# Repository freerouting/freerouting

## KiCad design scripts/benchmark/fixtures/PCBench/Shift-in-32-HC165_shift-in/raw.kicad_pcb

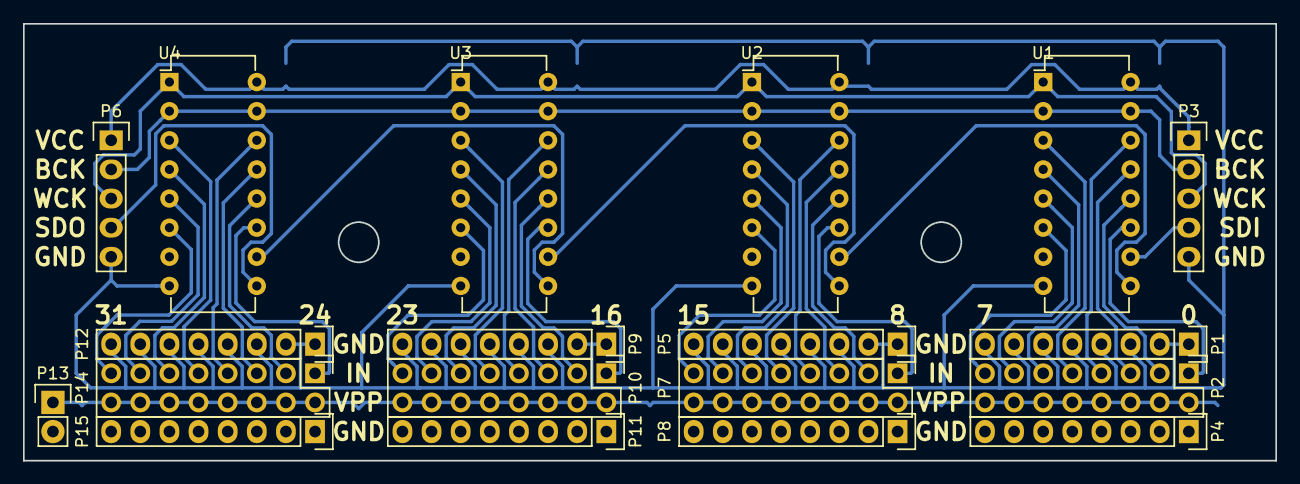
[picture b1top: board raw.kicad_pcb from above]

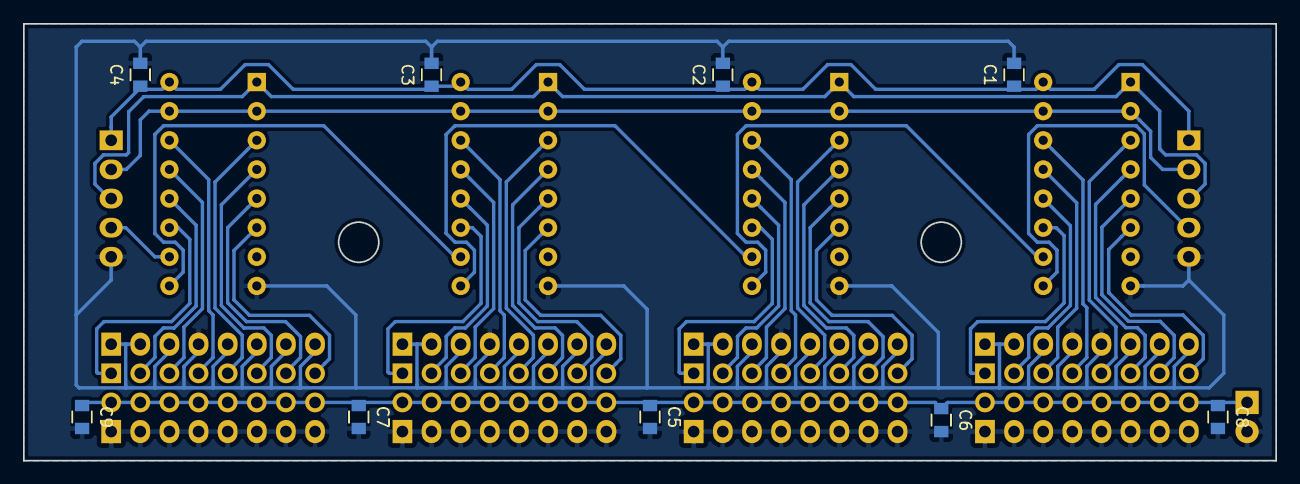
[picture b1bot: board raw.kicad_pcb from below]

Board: 2 copper layers, 109.2 x 38.1 mm, 28 parts (9 on the bottom side), 42 nets.

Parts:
C1, C2, C3, C4, C5, C6, C7, C8, C9: 10uF; C_0805
P1, P4, P5, P8, P9, P11, P12, P15: CONN_01X08; Pin_Header_Straight_1x08
P2, P7, P10, P14: CONN_02X08; Pin_Header_Straight_2x08
P3: EXPANSION; Pin_Header_Straight_1x05
P6: OUTPUT; Pin_Header_Straight_1x05
P13: CONN_01X02; Pin_Header_Straight_1x02
U1, U2, U3, U4: 74HC165; DIP-16_W7.62mm

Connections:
/BCK: P3.2, P6.2, U1.2, U1.15, U2.2, U2.15, U3.2, U3.15, U4.2, U4.15
/IN0: P2.1, U1.11
/IN1: P2.3, U1.12
/IN2: P2.5, U1.13
/IN3: P2.7, U1.14
/IN4: P2.9, U1.3
/IN5: P2.11, U1.4
/IN6: P2.13, U1.5
/IN7: P2.15, U1.6
/IN8: P7.1, U2.11
/IN9: P7.3, U2.12
/IN10: P7.5, U2.13
/IN11: P7.7, U2.14
/IN12: P7.9, U2.3
/IN13: P7.11, U2.4
/IN14: P7.13, U2.5
/IN15: P7.15, U2.6
/IN16: P10.1, U3.11
/IN17: P10.3, U3.12
/IN18: P10.5, U3.13
/IN19: P10.7, U3.14
/IN20: P10.9, U3.3
/IN21: P10.11, U3.4
/IN22: P10.13, U3.5
/IN23: P10.15, U3.6
/IN24: P14.1, U4.11
/IN25: P14.3, U4.12
/IN26: P14.5, U4.13
/IN27: P14.7, U4.14
/IN28: P14.9, U4.3
/IN29: P14.11, U4.4
/IN30: P14.13, U4.5
/IN31: P14.15, U4.6
/SDI: P3.4, U1.10
/SDO: P6.4, U4.9
/WCK: P3.3, P6.3, U1.1, U2.1, U3.1, U4.1
GND: C1.2, C2.2, C3.2, C4.2, C5.2, C6.2, C7.2, C8.2, C9.2, P1.1, P1.2, P1.3, P1.4, P1.5, P1.6, P1.7, P1.8, P3.5, P4.1, P4.2, P4.3, P4.4, P4.5, P4.6, P4.7, P4.8, P5.1, P5.2, P5.3, P5.4, P5.5, P5.6, P5.7, P5.8, P6.5, P8.1, P8.2, P8.3, P8.4, P8.5, P8.6, P8.7, P8.8, P9.1, P9.2, P9.3, P9.4, P9.5, P9.6, P9.7, P9.8, P11.1, P11.2, P11.3, P11.4, P11.5, P11.6, P11.7, P11.8, P12.1, P12.2, P12.3, P12.4, P12.5, P12.6, P12.7, P12.8, P13.2, P15.1, P15.2, P15.3, P15.4, P15.5, P15.6, P15.7, P15.8, U1.8, U2.8, U3.8, U4.8
unnamed: U1.9, U2.10
unnamed: U2.9, U3.10
unnamed: U3.9, U4.10
VCC: C1.1, C2.1, C3.1, C4.1, P3.1, P6.1, U1.16, U2.16, U3.16, U4.16
VPP: C5.1, C6.1, C7.1, C8.1, C9.1, P2.2, P2.4, P2.6, P2.8, P2.10, P2.12, P2.14, P2.16, P7.2, P7.4, P7.6, P7.8, P7.10, P7.12, P7.14, P7.16, P10.2, P10.4, P10.6, P10.8, P10.10, P10.12, P10.14, P10.16, P13.1, P14.2, P14.4, P14.6, P14.8, P14.10, P14.12, P14.14, P14.16

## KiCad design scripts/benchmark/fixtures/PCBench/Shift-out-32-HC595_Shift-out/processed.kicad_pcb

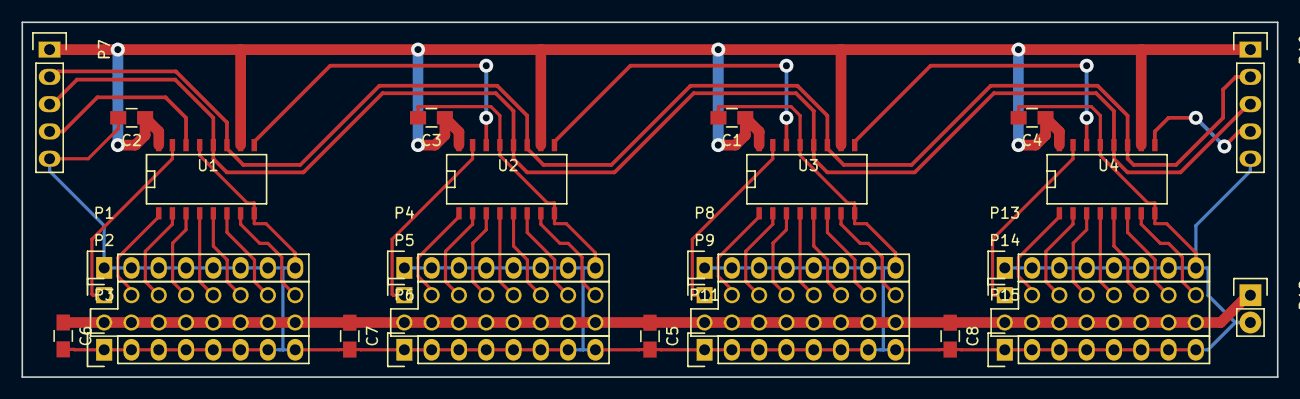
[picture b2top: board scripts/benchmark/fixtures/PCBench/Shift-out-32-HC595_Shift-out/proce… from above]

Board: 2 copper layers, 116.8 x 33.0 mm, 27 parts (0 on the bottom side), 42 nets.

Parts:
C1, C2, C3, C4, C5, C6, C7, C8: 1uF; C_0805_HandSoldering
P1, P3, P4, P6, P8, P11, P13, P15: CONN_01X08; Socket_Strip_Straight_1x08
P2, P5, P9, P14: CONN_02X08; Socket_Strip_Straight_2x08
P7: INPUT; Socket_Strip_Straight_1x05
P10: EXPANSION; Socket_Strip_Straight_1x05
P12: CONN_01X02; Socket_Strip_Straight_1x02
U1, U2, U3, U4: 74HC595; SO-16-N

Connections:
/BCK: P7.2, P10.2, U1.11, U2.11, U3.11, U4.11
/Q0: P2.1, U1.15
/Q1: P2.3, U1.1
/Q2: P2.5, U1.2
/Q3: P2.7, U1.3
/Q4: P2.9, U1.4
/Q5: P2.11, U1.5
/Q6: P2.13, U1.6
/Q7: P2.15, U1.7
/Q8: P5.1, U2.15
/Q9: P5.3, U2.1
/Q10: P5.5, U2.2
/Q11: P5.7, U2.3
/Q12: P5.9, U2.4
/Q13: P5.11, U2.5
/Q14: P5.13, U2.6
/Q15: P5.15, U2.7
/Q16: P9.1, U3.15
/Q17: P9.3, U3.1
/Q18: P9.5, U3.2
/Q19: P9.7, U3.3
/Q20: P9.9, U3.4
/Q21: P9.11, U3.5
/Q22: P9.13, U3.6
/Q23: P9.15, U3.7
/Q24: P14.1, U4.15
/Q25: P14.3, U4.1
/Q26: P14.5, U4.2
/Q27: P14.7, U4.3
/Q28: P14.9, U4.4
/Q29: P14.11, U4.5
/Q30: P14.13, U4.6
/Q31: P14.15, U4.7
/SDI: P7.4, U1.14
/SDO: P10.4, U4.9
/WCK: P7.3, P10.3, U1.12, U2.12, U3.12, U4.12
GND: C1.2, C2.2, C3.2, C4.2, C5.2, C6.2, C7.2, C8.2, P1.1, P1.2, P1.3, P1.4, P1.5, P1.6, P1.7, P1.8, P3.1, P3.2, P3.3, P3.4, P3.5, P3.6, P3.7, P3.8, P4.1, P4.2, P4.3, P4.4, P4.5, P4.6, P4.7, P4.8, P6.1, P6.2, P6.3, P6.4, P6.5, P6.6, P6.7, P6.8, P7.5, P8.1, P8.2, P8.3, P8.4, P8.5, P8.6, P8.7, P8.8, P10.5, P11.1, P11.2, P11.3, P11.4, P11.5, P11.6, P11.7, P11.8, P12.2, P13.1, P13.2, P13.3, P13.4, P13.5, P13.6, P13.7, P13.8, P15.1, P15.2, P15.3, P15.4, P15.5, P15.6, P15.7, P15.8, U1.8, U1.13, U2.8, U2.13, U3.8, U3.13, U4.8, U4.13
unnamed: U1.9, U2.14
unnamed: U2.9, U3.14
unnamed: U3.9, U4.14
VCC: C1.1, C2.1, C3.1, C4.1, P7.1, P10.1, U1.10, U1.16, U2.10, U2.16, U3.10, U3.16, U4.10, U4.16
VPP: C5.1, C6.1, C7.1, C8.1, P2.2, P2.4, P2.6, P2.8, P2.10, P2.12, P2.14, P2.16, P5.2, P5.4, P5.6, P5.8, P5.10, P5.12, P5.14, P5.16, P9.2, P9.4, P9.6, P9.8, P9.10, P9.12, P9.14, P9.16, P12.1, P14.2, P14.4, P14.6, P14.8, P14.10, P14.12, P14.14, P14.16

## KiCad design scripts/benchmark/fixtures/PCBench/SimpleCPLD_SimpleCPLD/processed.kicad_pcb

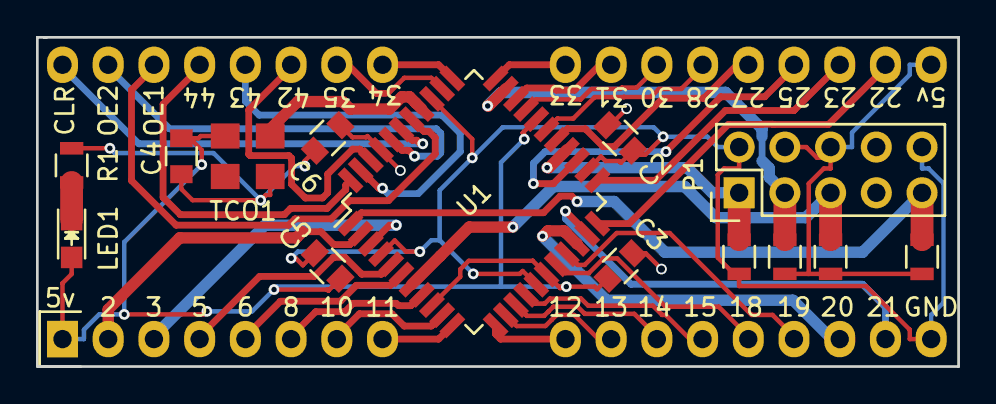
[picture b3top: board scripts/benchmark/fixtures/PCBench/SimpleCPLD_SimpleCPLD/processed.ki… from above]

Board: 4 copper layers, 51.2 x 18.3 mm, 16 parts (0 on the bottom side), 39 nets.

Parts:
C2, C3, C4, C5, C6: .1u; C_0805
LED1: LED; LED-0805
P1: CONN_02X05; Pin_Header_Straight_2x05
P2: CONN_01X17; Pin_Header_Straight_1x17
P3: CONN_01X17; Pin_Header_Straight_1x17B
R1: 1K; R_0805
R2, R3, R4, R5: 10K; R_0805
TCO1: KC5032A25_OSC; TCO-4
U1: EPM7064_TQFP; TQFP-44_10x10mm_Pitch0.8mm

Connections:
CLOCK: TCO1.3, U1.37
CLR: P3.1, U1.39
GND: C2.2, C3.2, C4.2, C5.2, C6.2, P1.2, P1.10, P2.17, R1.1, R2.2, TCO1.2, U1.4, U1.16, U1.24, U1.36
IO2: P2.2, U1.2
IO3: P2.3, U1.3
IO5: P2.4, U1.5
IO6: P2.5, U1.6
IO8: P2.6, U1.8
IO10: P2.7, U1.10
IO11: P2.8, U1.11
IO12: P2.9, U1.12
IO13: P2.10, U1.13
IO14: P2.11, U1.14
IO15: P2.12, U1.15
IO18: P2.13, U1.18
IO19: P2.14, U1.19
IO20: P2.15, U1.20
IO21: P2.16, U1.21
IO22: P3.16, U1.22
IO23: P3.15, U1.23
IO25: P3.14, U1.25
IO27: P3.13, U1.27
IO28: P3.12, U1.28
IO30: P3.11, U1.30
IO31: P3.10, U1.31
IO33: P3.9, U1.33
IO34: P3.8, U1.34
IO35: P3.7, U1.35
IO42: P3.6, U1.42
IO43: P3.5, U1.43
IO44: P3.4, U1.44
unnamed: LED1.1, R1.2
OE1: P3.3, U1.38
OE2: P3.2, U1.40
TCK: P1.1, R2.1, U1.26
TDI: P1.9, R5.1, U1.1
TDO: P1.3, R3.1, U1.32
TMS: P1.5, R4.1, U1.7
VCC: C2.1, C3.1, C4.1, C5.1, C6.1, LED1.2, P1.4, P1.6, P2.1, P3.17, R3.2, R4.2, R5.2, TCO1.4, U1.9, U1.17, U1.29, U1.41

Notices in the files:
scripts/benchmark/fixtures/PCBench/Shift-out-32-HC595_Shift-out/processed.kicad_pcb:
(c) 2016 Lucas V. Hartmann
